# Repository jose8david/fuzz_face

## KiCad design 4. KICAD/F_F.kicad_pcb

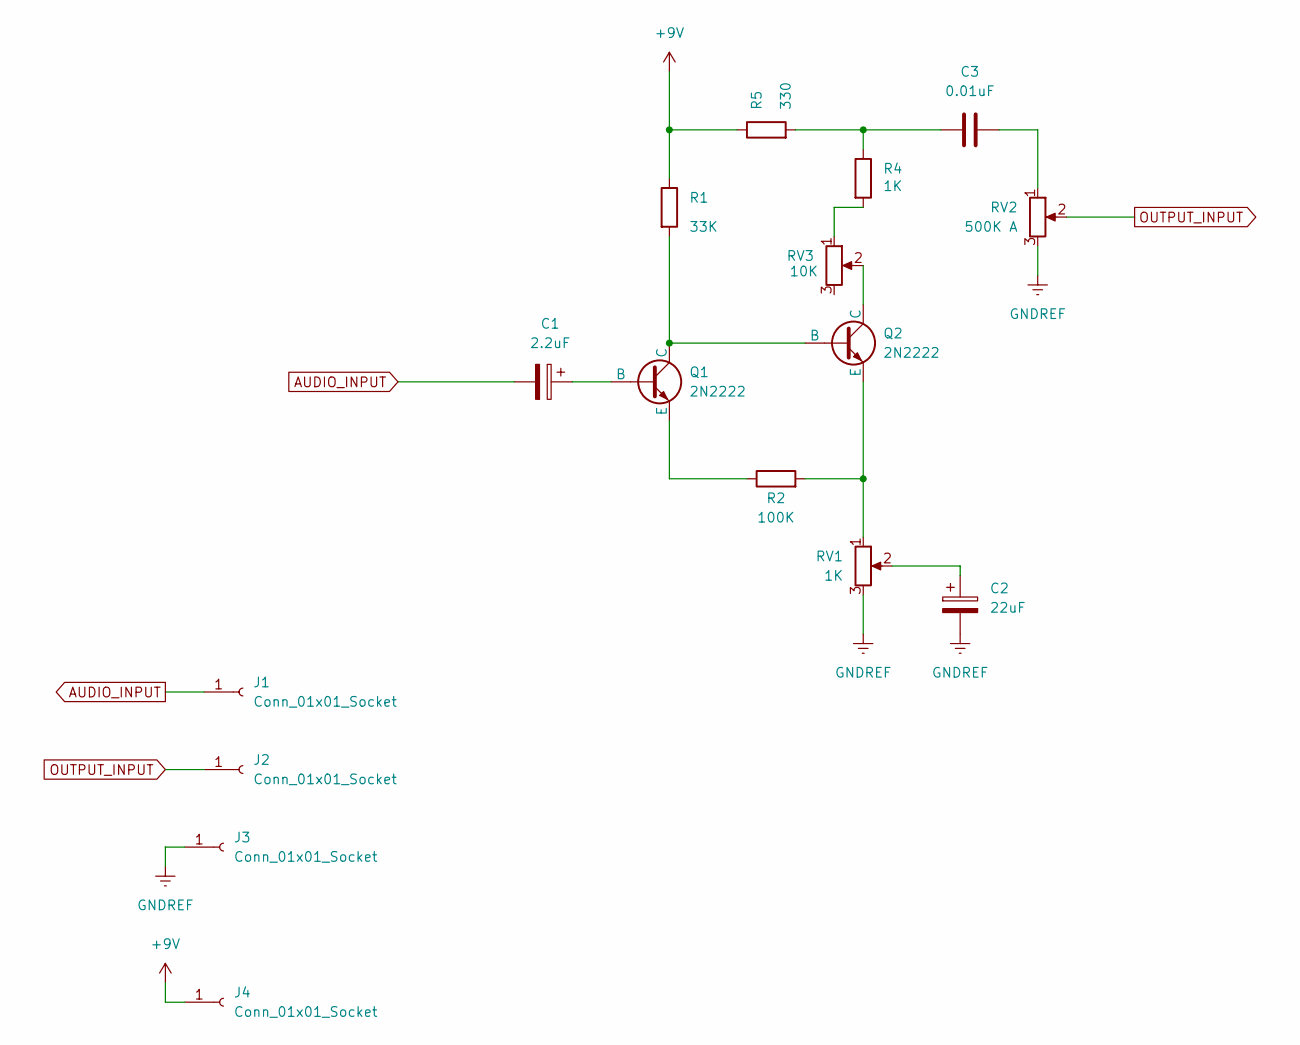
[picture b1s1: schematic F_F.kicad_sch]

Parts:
C1: 2.2uF; CP_Radial_D5.0mm_P2.50mm
C2: 22uF; CP_Radial_D5.0mm_P2.50mm
C3: 0.01uF; C_Disc_D3.4mm_W2.1mm_P2.50mm
J1, J2, J3, J4: Conn_01x01_Socket; Single_Conn
Q1, Q2: 2N2222; TO-92L_Inline
R1: 33K; R_Axial_DIN0207_L6.3mm_D2.5mm_P10.16mm_Horizontal
R2: 100K; R_Axial_DIN0207_L6.3mm_D2.5mm_P10.16mm_Horizontal
R4: 1K; R_Axial_DIN0207_L6.3mm_D2.5mm_P10.16mm_Horizontal
R5: 330; R_Axial_DIN0207_L6.3mm_D2.5mm_P10.16mm_Horizontal
RV1: 1K; pot_barato
RV2: 500K A; pot_barato
RV3: 10K; Trimmer

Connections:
+9V: J4.1, R1.1, R5.1
AUDIO_INPUT: C1.2, J1.1
GNDREF: C2.2, J3.1, RV1.3, RV2.3
unnamed: C2.1, RV1.2
unnamed: C3.1, R4.1, R5.2
unnamed: C3.2, RV2.1
unnamed: C1.1, Q1.2 (B)
unnamed: Q1.1 (C), Q2.2 (B), R1.2
unnamed: Q1.3 (E), R2.1
unnamed: Q2.1 (C), RV3.2
unnamed: Q2.3 (E), R2.2, RV1.1
unnamed: R4.2, RV3.1
OUTPUT_INPUT: J2.1, RV2.2

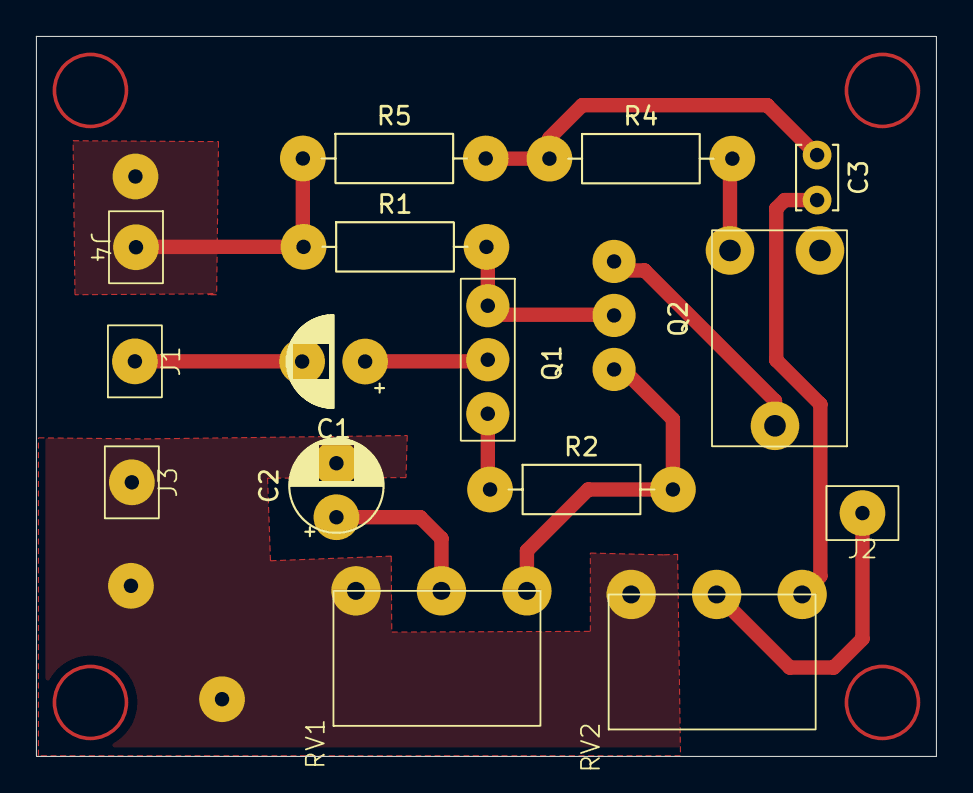
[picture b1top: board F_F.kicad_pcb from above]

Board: 2 copper layers, 50.0 x 40.0 mm, 16 parts (0 on the bottom side), 13 nets.

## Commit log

2026-01-15 Init commit
2026-01-16 Archivos LPKF
